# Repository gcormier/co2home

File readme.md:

# co2home
This device interfaces with an MH-Z19 and makes the data available in home assistant via esphome. It could also work with any other software you'd like on an ESP32. It is powered and programmed via a USB-C port.

Phyiscally, this should also work with the Senseair S8 as it has the same pinouts. ESPHome provides a <a href="https://esphome.io/components/sensor/senseair.html">different block</a> to work with this.

There may be other clones out there as well such as the SYP50-A-5K.

## Narrative
With COVID hitting and basically spending the tail end of Winter and a lot of spring indoors 24x7, I really wanted to check out the indoor air quality. My house does have an ERV, but it was basically a guessing game. No matter how efficient an ERV/HRV is, there is still a penalty to pay. I wanted a way to quantify the levels to adjust my HRV accordingly.

Now with HA and Grafana, I've dialed it in. I have the sensor in my bedroom, but I have just built another board, and I hope to put it somewhere near (or in) a duct to meter the overall CO2 levels in the house. I do want my air handler fan settings to keep the bedroom to acceptable levels at night.

I've found now that 10 minutes an hour is not quite enough ERV time with the CFM I've selected to run it at. Throughout the day, the CO2 level will slowly rise. However, at 20 minutes/hour, it is bringing in enough fresh air to keep levels from rising too much!

Overkill, sure, but hey, why not?

## Programming
The new revision uses an ESP32-C3-MINI-1 which has native USB support. This means the code can be flashed via USB. The first time this is done, you must HOLD the button while plugging in the USB-C cable to force it in programming mode. Flash using `esphome` or any other flasher. Any subsequent flashes do not need any button pushes.

As a backup, there is a programming header - the pinout matches my esp32 programmer, <a href="https://github.com/gcormier/eflashy32/">eflashy32</a> if you are in need of a programmer as well.

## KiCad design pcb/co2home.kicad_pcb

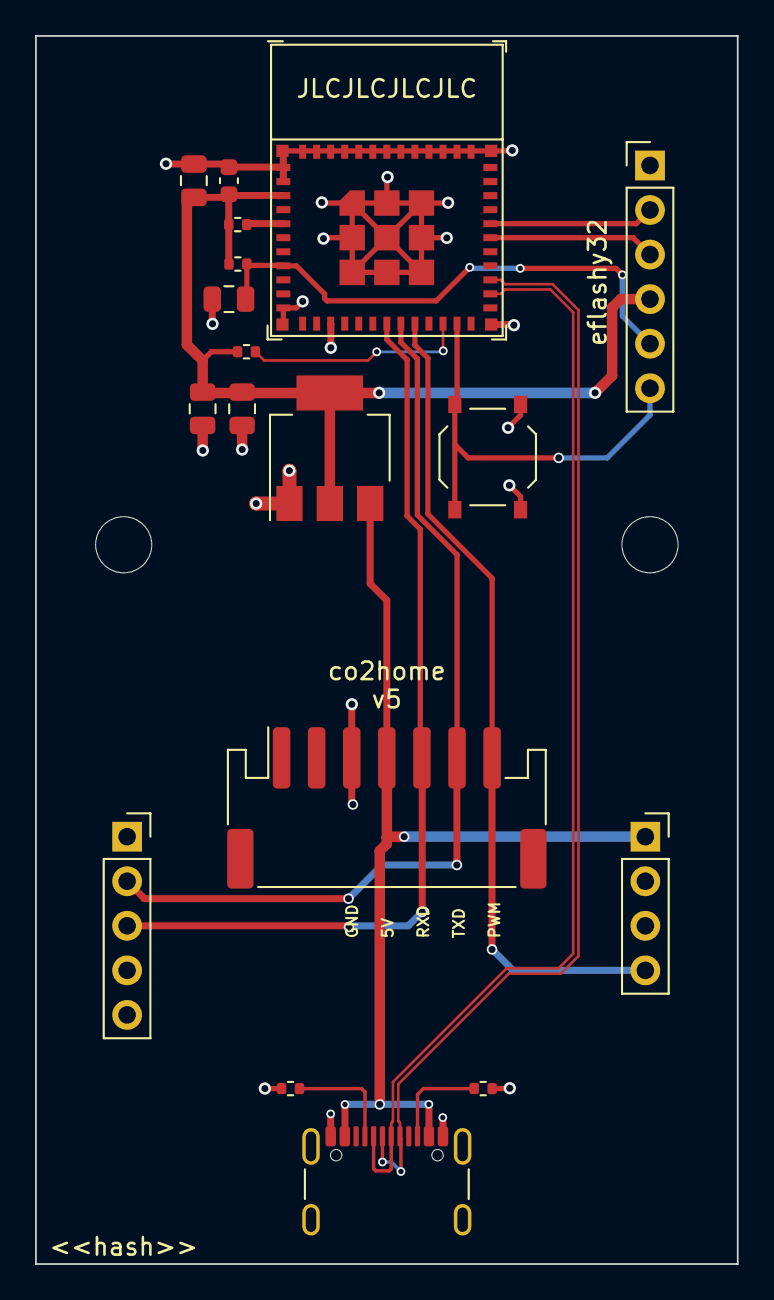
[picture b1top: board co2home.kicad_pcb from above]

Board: 2 copper layers, 40.0 x 70.0 mm, 20 parts (0 on the bottom side), 16 nets.

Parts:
C4, C6, C7, C8: 10u; C_0805_2012Metric
C5: 0.1u; C_0603_1608Metric
H1, H2: MountingHole; MountingHole_3.2mm_M3
J1: eflashy32; PinHeader_1x06_P2.54mm_Vertical
J2: MH-Z19 L; PinSocket_1x05_P2.54mm_Vertical
J3: USBC; USB_C_Receptacle_GCT_USB4105-xx-A_16P_TopMnt_Horizontal
J4: MH-Z19 R; PinSocket_1x04_P2.54mm_Vertical
J5: JST-PH; JST_PH_S7B-PH-SM4-TB_1x07-1MP_P2.00mm_Horizontal
R2, R3: 5k1; R_0402_1005Metric
R4, R5, R6: 10k; R_0402_1005Metric
SW1: RESET; SW_Push_1P1T_XKB_TS-1187A
U1: ESP32-C3-MINI-1
U4: AMS1117-3.3; SOT-223-3_TabPin2

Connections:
+3V3: C5.2, C6.2, C7.2, C8.2, J1.4, R4.1, R5.1, R6.1, U1.3 (3V3), U4.2 (VO)
+5V: J3.A4 (VBUS), J3.A9 (VBUS), J3.B4 (VBUS), J3.B9 (VBUS), J4.1, J5.4, U4.3 (VI)
/EN: C4.2, J1.5, R4.2, U1.8 (EN/CHIP_PU)
/GPIO0: J1.6, SW1.1 (A), U1.23 (GPIO9)
/PROGRXD: J1.3, U1.30 (GPIO20/U0RXD)
/PROGTXD: J1.2, U1.31 (GPIO21/U0TXD)
D+: J3.A6 (D+), J3.B6 (D+), U1.27 (GPIO19/USB_D+)
D-: J3.A7 (D-), J3.B7 (D-), U1.26 (GPIO18/USB_D-)
GND: C4.1, C5.1, C6.1, C7.1, C8.1, J1.1, J3.A1 (GND), J3.A12 (GND), J3.B1 (GND), J3.B12 (GND), J4.2, J5.3, R2.2, R3.2, SW1.2 (B), U1.1 (GND), U1.2 (GND), U1.11 (GND), U1.14 (GND), U1.36 (GND), U1.37 (GND), U1.38 (GND), U1.39 (GND), U1.40 (GND), U1.41 (GND), U1.42 (GND), U1.43 (GND), U1.44 (GND), U1.45 (GND), U1.46 (GND), U1.47 (GND), U1.48 (GND), U1.49 (GND), U1.50 (GND), U1.51 (GND), U1.52 (GND), U1.53 (GND), U4.1 (GND)
unnamed: J3.A5 (CC1), R3.1
unnamed: J3.B5 (CC2), R2.1
unnamed: R5.2, U1.5 (GPIO2/ADC1_CH2)
unnamed: R6.2, U1.22 (GPIO8)
PWM: J4.4, J5.7, U1.20 (GPIO6)
RXD: J2.3, J5.5, U1.18 (GPIO4/ADC1_CH4)
TXD: J2.2, J5.6, U1.19 (GPIO5/ADC2_CH0)

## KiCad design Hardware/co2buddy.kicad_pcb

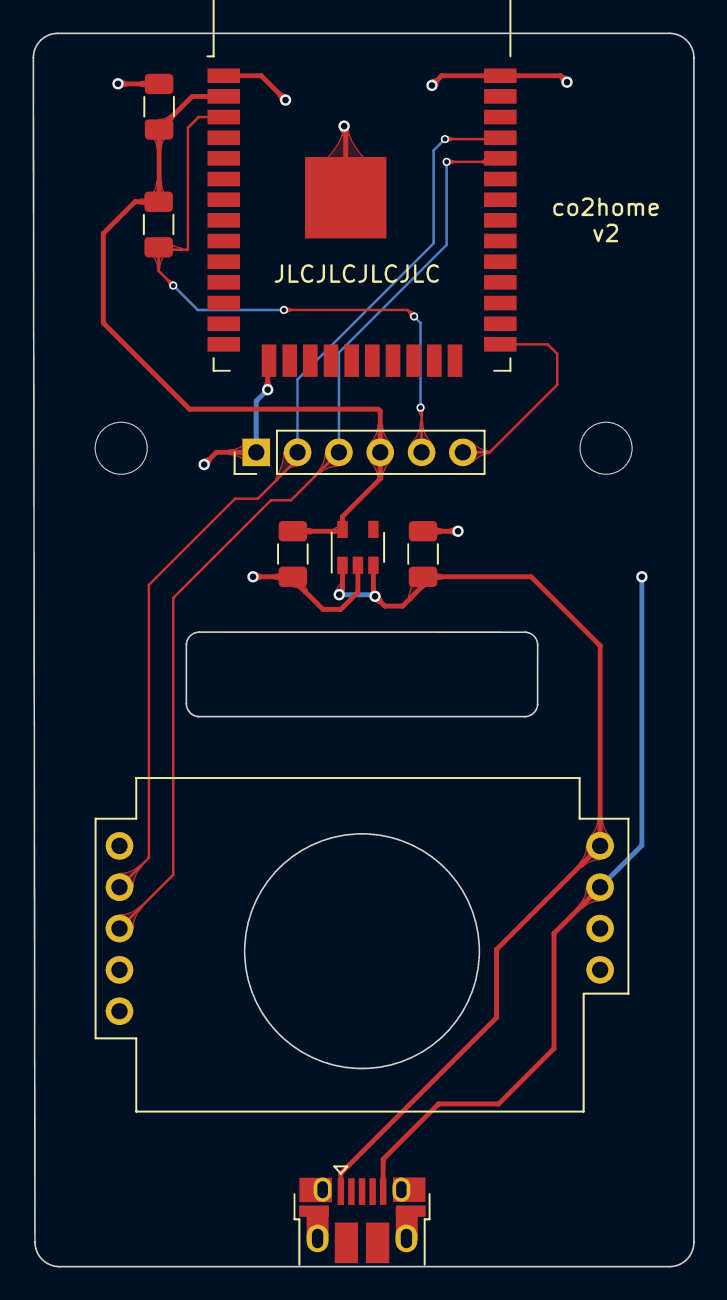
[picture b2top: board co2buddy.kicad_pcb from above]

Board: 2 copper layers, 40.6 x 75.8 mm, 9 parts (0 on the bottom side), 7 nets.

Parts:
C1, C2: 1uF; C_1206_3216Metric
C3: 10uF; C_1206_3216Metric
J1: esp32buddy; PinHeader_1x06_P2.54mm_Vertical
J2: USB_B_Micro; USB_Micro-B_Amphenol_10103594-0001LF_Horizontal
R1: 100k; R_1206_3216Metric
U1: MH-Z19
U2: TLV75533PDBV; SOT-23-5
U3: ESP32-WROOM-32D; ESP32-WROOM-32

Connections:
+3V3: C2.1, C3.2, J1.4, R1.2, U2.5, U3.2
/EN: J1.5, R1.1, U3.3
/GPIO0: J1.6, U3.25
/RXD: J1.3, U1.3, U3.34
/TXD: J1.2, U1.2, U3.35
GND: C1.1, C2.2, C3.1, J1.1, J2.5, U1.7, U2.2, U3.1, U3.15, U3.38, U3.39
VBUS: C1.2, J2.1, U1.6, U2.1, U2.3

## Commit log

2020-06-22 initial
2020-07-09 actually v2?
2020-07-09 rename esphome config file
2020-07-20 fix pins
2020-08-07 docs
2020-10-26 add senseair s8 note
2020-11-04 link to store
2021-03-06 fix fallback hotspot name
2021-03-06 fallback password and other names
2022-07-18 longer pw
2023-04-02 kicad v7
2023-09-20 newness
2023-09-20 ignorey
2023-09-20 kibot
2023-09-20 actinos
2023-09-20 move actions
2023-09-20 try to remove 1 model
2023-09-20 readme update
2023-09-24 disable
2023-09-24 re-enable
2023-09-28 remove kicad model
2023-09-28 silkscreen for pins
2023-09-28 panel
2023-09-28 PN for headers
2023-09-28 2layer
2023-10-01 badge
2023-10-17 esp32c3mini changes
2023-11-03 3d printed case
